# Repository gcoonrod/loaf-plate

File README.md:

# The LoafPlate

The LoafPlate is a DIY electronics and prototyping tool designed to make interacting with standard
(830 tie-point) breadboards easier. The base PCB is intended to be reused in other designs to allow for the
creation of "plates" (like Arduino shields or RPi hats), which can provide any number of features to support or interact with the LoafPlate and its breadboard.

## The LP Extension

Like the hats and shields that inspired it, the LoafPlate uses a "standard" or shared interface called an LP Extension. The LP Extension is designed to share power, ground, and six GPIO signals between any number of stacked plates. A 10 pin right angle IDC connector with 2.54mm pitch was chosen as it can be used with ribbon cables which are easy for hobbyists to buy or assemble.

Six GPIOs isn't much (not even a full byte!) but unlike an Arduino or Raspberry Pi the LoafPlate is focused
on supporting breadboard prototyping and its design is intended to leave as much open space around the edges of each plate as possible. This space will be used by other plates to provide easy access to sockets, pin headers, screw terminals, buttons, and more.

## The Standard Plates

Along with the LoafPlate, this repo contains designs for a number of other plates which are meant to provide an example of a complete (if simple) circuit prototyping environment or hardware IDE if you will.

### The PSUPlate

All electronics projects need power, as such the first accessory plate for the LoafPlate is the PSUPlate. As the name suggests, it is a power supply unit designed to connect to a common ATX power supply via the 24 pin ATX 2.0 connector. The PSUPlate provides access to 3.3V, 5V, and 12V power rails and uses readily available blade type fuses for circuit protection.

### The TestPlate

Interacting with digital circuits can be difficult and frustrating without tools like an oscilloscope or
logic analyzer. However, those tools can be quite expensive. The TestPlate is designed to act as a circuit
tester, allowing the user to drive two chains of shift registers which allows them to set 32 input values and read 32 output results.

This picture is from an early design of the TestPlate before the LP Extension was finalized.

## Extra Plates

The following are early designs and ideas for kinds of plates that can be created for the LoafPlate environment.

### The ClockPlate

Based on the work of Bed Eater and Rehsd, the ClockPlate is a clock signal generator for 5V logic circuits.
It provides three clocking modes: Manual pulse, Adjustable slow (555), and fixed fast (crystal oscillator). In addition to the standard LP Extension, it exposes two pair of outputs (clock and reset) and accepts a single input (halt).

## Project Goals

I am a software engineer by trade and training. Hardware and digital circuits have always seemed the realm of sorcerers and the dark arts to me. Watching YouTube videos from people like Ben Eater, Rehsd, and Francis Stokes (Low Byte Productions), has really opened my eyes to how accessible hardware and computer design has become. My goal for the LoafPlate project is above all, learning. I want to understand how the computers I write programs for _actually_ work and I want to design circuits, systems, and devices to help further that understanding.

This repo is my RFC, my Request for Comment. Please, point out my mistakes, correct my bad assumptions, suggest improvements, help me _learn_.

### Links & Resources

Tools:

- [KiCad](https://www.kicad.org/): All circuits and PCBs were designed with KiCad V6.

YouTube Creators:

- [Ben Eater](https://www.youtube.com/@BenEater)
- [Rehsd](https://www.youtube.com/@rehsd)
- [Low Byte Productions](https://www.youtube.com/@LowByteProductions)
- [Phil's Lab](https://www.youtube.com/@PhilsLab)
- [Fabian Schuiki](https://www.youtube.com/@fabianschuiki)
- [Adrien Kohlbecker](https://www.youtube.com/@akohlbecker)

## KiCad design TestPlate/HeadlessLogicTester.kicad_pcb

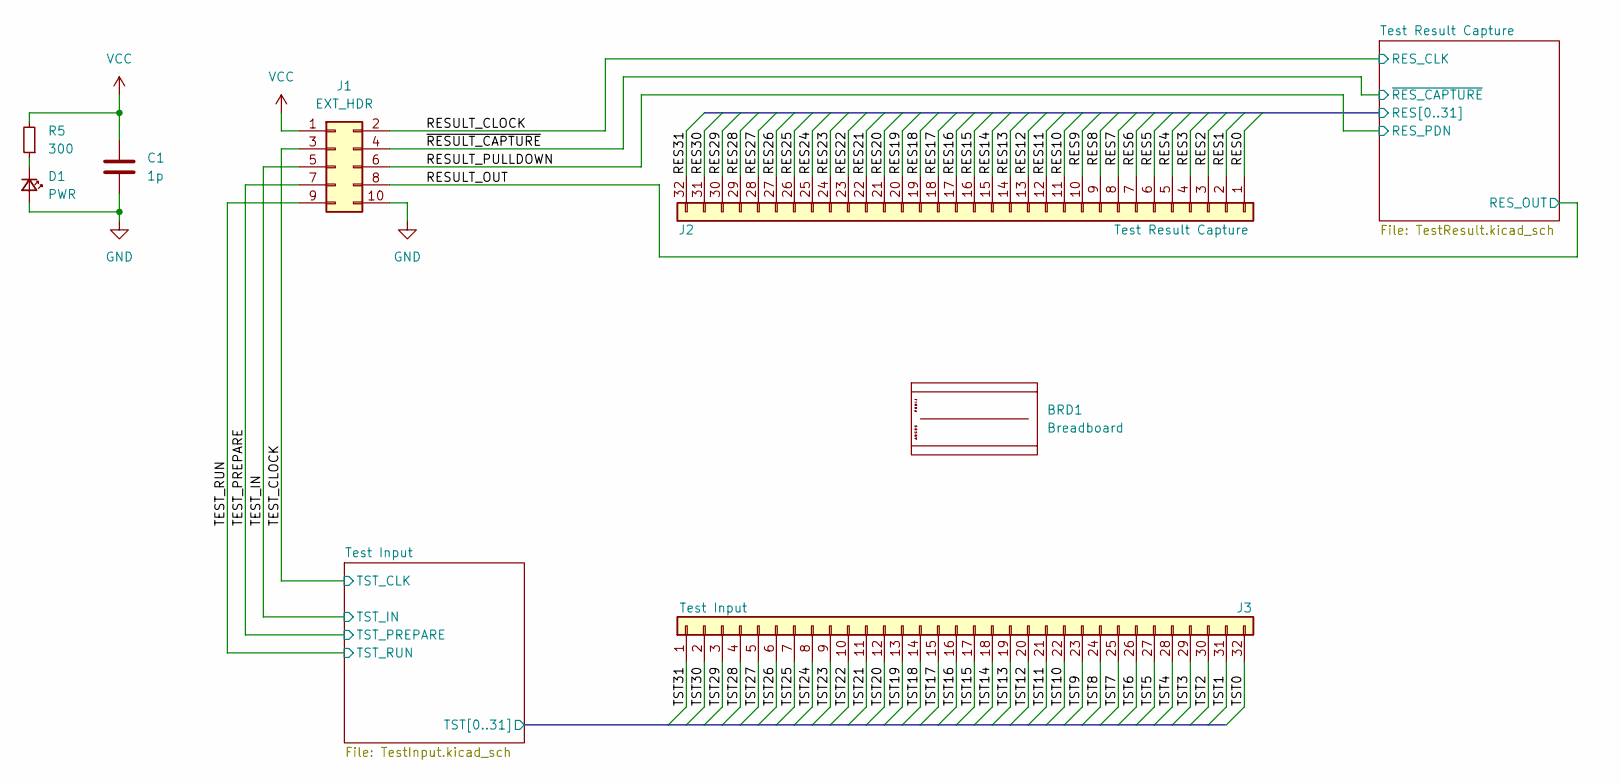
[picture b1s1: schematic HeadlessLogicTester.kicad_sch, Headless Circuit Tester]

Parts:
BRD1: Breadboard; Breadboard_Busx02_Terminalx01_Tiesx830_WithMounts
C1: 1p; C_1206_3216Metric_Pad1.33x1.80mm_HandSolder
D1: PWR; LED_1206_3216Metric_Pad1.42x1.75mm_HandSolder
J1: EXT_HDR; PinSocket_2x05_P2.54mm_Horizontal
J2: Test Result Capture; PinSocket_1x32_P2.54mm_Horizontal
J3: Test Input; PinSocket_1x32_P2.54mm_Horizontal
R5: 300; R_1206_3216Metric_Pad1.30x1.75mm_HandSolder

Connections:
/RESULT_CLOCK: J1.2; also elsewhere on the board
/RESULT_OUT: J1.8; also elsewhere on the board
/RESULT_PULLDOWN: J1.6; also elsewhere on the board
/TEST_CLOCK: J1.3; also elsewhere on the board
/TEST_IN: J1.5; also elsewhere on the board
/TEST_PREPARE: J1.7; also elsewhere on the board
/TEST_RUN: J1.9; also elsewhere on the board
/Test Input/TST0: J3.32; also elsewhere on the board
/Test Input/TST1: J3.31; also elsewhere on the board
/Test Input/TST2: J3.30; also elsewhere on the board
/Test Input/TST3: J3.29; also elsewhere on the board
/Test Input/TST4: J3.28; also elsewhere on the board
/Test Input/TST5: J3.27; also elsewhere on the board
/Test Input/TST6: J3.26; also elsewhere on the board
/Test Input/TST7: J3.25; also elsewhere on the board
/Test Input/TST8: J3.24; also elsewhere on the board
/Test Input/TST9: J3.23; also elsewhere on the board
/Test Input/TST10: J3.22; also elsewhere on the board
/Test Input/TST11: J3.21; also elsewhere on the board
/Test Input/TST12: J3.20; also elsewhere on the board
/Test Input/TST13: J3.19; also elsewhere on the board
/Test Input/TST14: J3.18; also elsewhere on the board
/Test Input/TST15: J3.17; also elsewhere on the board
/Test Input/TST16: J3.16; also elsewhere on the board
/Test Input/TST17: J3.15; also elsewhere on the board
/Test Input/TST18: J3.14; also elsewhere on the board
/Test Input/TST19: J3.13; also elsewhere on the board
/Test Input/TST20: J3.12; also elsewhere on the board
/Test Input/TST21: J3.11; also elsewhere on the board
/Test Input/TST22: J3.10; also elsewhere on the board
/Test Input/TST23: J3.9; also elsewhere on the board
/Test Input/TST24: J3.8; also elsewhere on the board
/Test Input/TST25: J3.7; also elsewhere on the board
/Test Input/TST26: J3.6; also elsewhere on the board
/Test Input/TST27: J3.5; also elsewhere on the board
/Test Input/TST28: J3.4; also elsewhere on the board
/Test Input/TST29: J3.3; also elsewhere on the board
/Test Input/TST30: J3.2; also elsewhere on the board
/Test Input/TST31: J3.1; also elsewhere on the board
/Test Result Capture/RES0: J2.1; also elsewhere on the board
/Test Result Capture/RES1: J2.2; also elsewhere on the board
/Test Result Capture/RES2: J2.3; also elsewhere on the board
/Test Result Capture/RES3: J2.4; also elsewhere on the board
/Test Result Capture/RES4: J2.5; also elsewhere on the board
/Test Result Capture/RES5: J2.6; also elsewhere on the board
/Test Result Capture/RES6: J2.7; also elsewhere on the board
/Test Result Capture/RES7: J2.8; also elsewhere on the board
/Test Result Capture/RES8: J2.9; also elsewhere on the board
/Test Result Capture/RES9: J2.10; also elsewhere on the board
/Test Result Capture/RES10: J2.11; also elsewhere on the board
/Test Result Capture/RES11: J2.12; also elsewhere on the board
/Test Result Capture/RES12: J2.13; also elsewhere on the board
/Test Result Capture/RES13: J2.14; also elsewhere on the board
/Test Result Capture/RES14: J2.15; also elsewhere on the board
/Test Result Capture/RES15: J2.16; also elsewhere on the board
/Test Result Capture/RES16: J2.17; also elsewhere on the board
/Test Result Capture/RES17: J2.18; also elsewhere on the board
/Test Result Capture/RES18: J2.19; also elsewhere on the board
/Test Result Capture/RES19: J2.20; also elsewhere on the board
/Test Result Capture/RES20: J2.21; also elsewhere on the board
/Test Result Capture/RES21: J2.22; also elsewhere on the board
/Test Result Capture/RES22: J2.23; also elsewhere on the board
/Test Result Capture/RES23: J2.24; also elsewhere on the board
/Test Result Capture/RES24: J2.25; also elsewhere on the board
/Test Result Capture/RES25: J2.26; also elsewhere on the board
/Test Result Capture/RES26: J2.27; also elsewhere on the board
/Test Result Capture/RES27: J2.28; also elsewhere on the board
/Test Result Capture/RES28: J2.29; also elsewhere on the board
/Test Result Capture/RES29: J2.30; also elsewhere on the board
/Test Result Capture/RES30: J2.31; also elsewhere on the board
/Test Result Capture/RES31: J2.32; also elsewhere on the board
/~RESULT_CAPTURE: J1.4; also elsewhere on the board
GND: C1.2, D1.2 (A), J1.10; also elsewhere on the board
unnamed: D1.1 (K), R5.1
VCC: C1.1, J1.1, R5.2; also elsewhere on the board

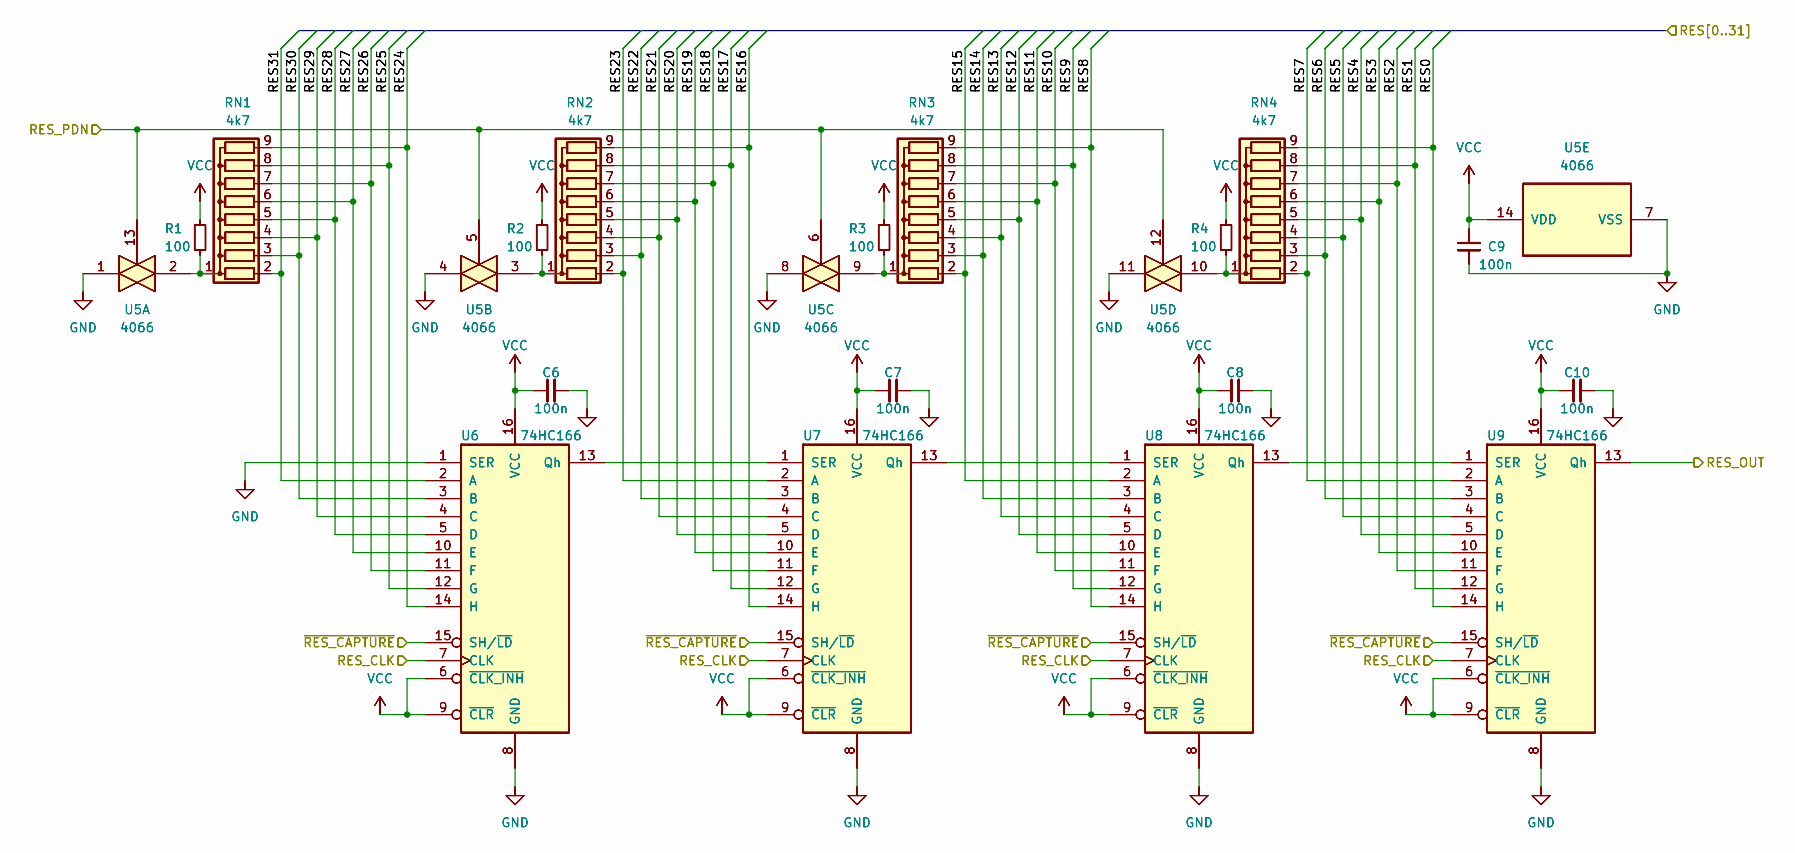
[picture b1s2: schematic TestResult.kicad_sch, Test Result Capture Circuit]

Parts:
C6, C7, C8, C9, C10: 100n; C_1206_3216Metric_Pad1.33x1.80mm_HandSolder
R1, R2, R3, R4: 100; C_1206_3216Metric_Pad1.33x1.80mm_HandSolder
RN1, RN2, RN3, RN4: 4k7; R_Array_SIP9
U5: 4066; DIP-14_W7.62mm_Socket
U6, U7, U8, U9: 74HC166; DIP-16_W7.62mm_Socket

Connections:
/RESULT_CLOCK: U6.7 (CLK), U7.7 (CLK), U8.7 (CLK), U9.7 (CLK); also elsewhere on the board
/RESULT_OUT: U9.13 (Qh); also elsewhere on the board
/RESULT_PULLDOWN: U5.5, U5.6, U5.12, U5.13; also elsewhere on the board
/Test Result Capture/RES0: RN4.9 (R8), U9.14 (H); also elsewhere on the board
/Test Result Capture/RES1: RN4.8 (R7), U9.12 (G); also elsewhere on the board
/Test Result Capture/RES2: RN4.7 (R6), U9.11 (F); also elsewhere on the board
/Test Result Capture/RES3: RN4.6 (R5), U9.10 (E); also elsewhere on the board
/Test Result Capture/RES4: RN4.5 (R4), U9.5 (D); also elsewhere on the board
/Test Result Capture/RES5: RN4.4 (R3), U9.4 (C); also elsewhere on the board
/Test Result Capture/RES6: RN4.3 (R2), U9.3 (B); also elsewhere on the board
/Test Result Capture/RES7: RN4.2 (R1), U9.2 (A); also elsewhere on the board
/Test Result Capture/RES8: RN3.9 (R8), U8.14 (H); also elsewhere on the board
/Test Result Capture/RES9: RN3.8 (R7), U8.12 (G); also elsewhere on the board
/Test Result Capture/RES10: RN3.7 (R6), U8.11 (F); also elsewhere on the board
/Test Result Capture/RES11: RN3.6 (R5), U8.10 (E); also elsewhere on the board
/Test Result Capture/RES12: RN3.5 (R4), U8.5 (D); also elsewhere on the board
/Test Result Capture/RES13: RN3.4 (R3), U8.4 (C); also elsewhere on the board
/Test Result Capture/RES14: RN3.3 (R2), U8.3 (B); also elsewhere on the board
/Test Result Capture/RES15: RN3.2 (R1), U8.2 (A); also elsewhere on the board
/Test Result Capture/RES16: RN2.9 (R8), U7.14 (H); also elsewhere on the board
/Test Result Capture/RES17: RN2.8 (R7), U7.12 (G); also elsewhere on the board
/Test Result Capture/RES18: RN2.7 (R6), U7.11 (F); also elsewhere on the board
/Test Result Capture/RES19: RN2.6 (R5), U7.10 (E); also elsewhere on the board
/Test Result Capture/RES20: RN2.5 (R4), U7.5 (D); also elsewhere on the board
/Test Result Capture/RES21: RN2.4 (R3), U7.4 (C); also elsewhere on the board
/Test Result Capture/RES22: RN2.3 (R2), U7.3 (B); also elsewhere on the board
/Test Result Capture/RES23: RN2.2 (R1), U7.2 (A); also elsewhere on the board
/Test Result Capture/RES24: RN1.9 (R8), U6.14 (H); also elsewhere on the board
/Test Result Capture/RES25: RN1.8 (R7), U6.12 (G); also elsewhere on the board
/Test Result Capture/RES26: RN1.7 (R6), U6.11 (F); also elsewhere on the board
/Test Result Capture/RES27: RN1.6 (R5), U6.10 (E); also elsewhere on the board
/Test Result Capture/RES28: RN1.5 (R4), U6.5 (D); also elsewhere on the board
/Test Result Capture/RES29: RN1.4 (R3), U6.4 (C); also elsewhere on the board
/Test Result Capture/RES30: RN1.3 (R2), U6.3 (B); also elsewhere on the board
/Test Result Capture/RES31: RN1.2 (R1), U6.2 (A); also elsewhere on the board
/~RESULT_CAPTURE: U6.15 (SH/~LD), U7.15 (SH/~LD), U8.15 (SH/~LD), U9.15 (SH/~LD); also elsewhere on the board
GND: C6.2, C7.2, C8.2, C9.2, C10.2, U5.1, U5.4, U5.7 (VSS), U5.8, U5.11, U6.1 (SER), U6.8 (GND), U7.8 (GND), U8.8 (GND), U9.8 (GND); also elsewhere on the board
unnamed: R1.2, RN1.1 (common), U5.2
unnamed: R2.2, RN2.1 (common), U5.3
unnamed: R3.2, RN3.1 (common), U5.9
unnamed: R4.2, RN4.1 (common), U5.10
unnamed: U6.13 (Qh), U7.1 (SER)
unnamed: U7.13 (Qh), U8.1 (SER)
unnamed: U8.13 (Qh), U9.1 (SER)
VCC: C6.1, C7.1, C8.1, C9.1, C10.1, R1.1, R2.1, R3.1, R4.1, U5.14 (VDD), U6.6 (~CLK_INH), U6.9 (~CLR), U6.16 (VCC), U7.6 (~CLK_INH), U7.9 (~CLR), U7.16 (VCC), U8.6 (~CLK_INH), U8.9 (~CLR), U8.16 (VCC), U9.6 (~CLK_INH), U9.9 (~CLR), U9.16 (VCC); also elsewhere on the board

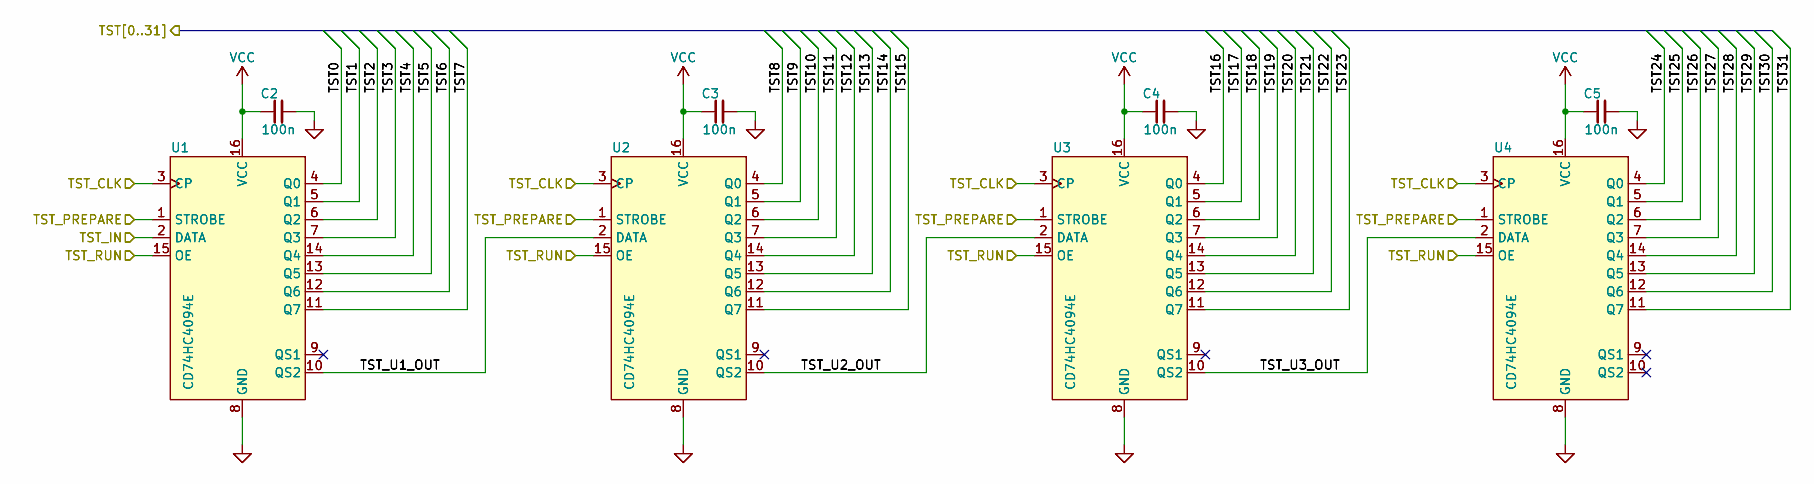
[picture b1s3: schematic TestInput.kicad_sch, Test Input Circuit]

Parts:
C2, C3, C4, C5: 100n; C_1206_3216Metric_Pad1.33x1.80mm_HandSolder
U1, U2, U3, U4: CD74HC4094E; DIP-16_W7.62mm_Socket

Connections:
/TEST_CLOCK: U1.3 (CP), U2.3 (CP), U3.3 (CP), U4.3 (CP); also elsewhere on the board
/TEST_IN: U1.2 (DATA); also elsewhere on the board
/TEST_PREPARE: U1.1 (STROBE), U2.1 (STROBE), U3.1 (STROBE), U4.1 (STROBE); also elsewhere on the board
/TEST_RUN: U1.15 (OE), U2.15 (OE), U3.15 (OE), U4.15 (OE); also elsewhere on the board
/Test Input/TST0: U1.4 (Q0); also elsewhere on the board
/Test Input/TST1: U1.5 (Q1); also elsewhere on the board
/Test Input/TST2: U1.6 (Q2); also elsewhere on the board
/Test Input/TST3: U1.7 (Q3); also elsewhere on the board
/Test Input/TST4: U1.14 (Q4); also elsewhere on the board
/Test Input/TST5: U1.13 (Q5); also elsewhere on the board
/Test Input/TST6: U1.12 (Q6); also elsewhere on the board
/Test Input/TST7: U1.11 (Q7); also elsewhere on the board
/Test Input/TST8: U2.4 (Q0); also elsewhere on the board
/Test Input/TST9: U2.5 (Q1); also elsewhere on the board
/Test Input/TST10: U2.6 (Q2); also elsewhere on the board
/Test Input/TST11: U2.7 (Q3); also elsewhere on the board
/Test Input/TST12: U2.14 (Q4); also elsewhere on the board
/Test Input/TST13: U2.13 (Q5); also elsewhere on the board
/Test Input/TST14: U2.12 (Q6); also elsewhere on the board
/Test Input/TST15: U2.11 (Q7); also elsewhere on the board
/Test Input/TST16: U3.4 (Q0); also elsewhere on the board
/Test Input/TST17: U3.5 (Q1); also elsewhere on the board
/Test Input/TST18: U3.6 (Q2); also elsewhere on the board
/Test Input/TST19: U3.7 (Q3); also elsewhere on the board
/Test Input/TST20: U3.14 (Q4); also elsewhere on the board
/Test Input/TST21: U3.13 (Q5); also elsewhere on the board
/Test Input/TST22: U3.12 (Q6); also elsewhere on the board
/Test Input/TST23: U3.11 (Q7); also elsewhere on the board
/Test Input/TST24: U4.4 (Q0); also elsewhere on the board
/Test Input/TST25: U4.5 (Q1); also elsewhere on the board
/Test Input/TST26: U4.6 (Q2); also elsewhere on the board
/Test Input/TST27: U4.7 (Q3); also elsewhere on the board
/Test Input/TST28: U4.14 (Q4); also elsewhere on the board
/Test Input/TST29: U4.13 (Q5); also elsewhere on the board
/Test Input/TST30: U4.12 (Q6); also elsewhere on the board
/Test Input/TST31: U4.11 (Q7); also elsewhere on the board
/Test Input/TST_U1_OUT: U1.10 (QS2), U2.2 (DATA)
/Test Input/TST_U2_OUT: U2.10 (QS2), U3.2 (DATA)
/Test Input/TST_U3_OUT: U3.10 (QS2), U4.2 (DATA)
GND: C2.2, C3.2, C4.2, C5.2, U1.8 (GND), U2.8 (GND), U3.8 (GND), U4.8 (GND); also elsewhere on the board
VCC: C2.1, C3.1, C4.1, C5.1, U1.16 (VCC), U2.16 (VCC), U3.16 (VCC), U4.16 (VCC); also elsewhere on the board

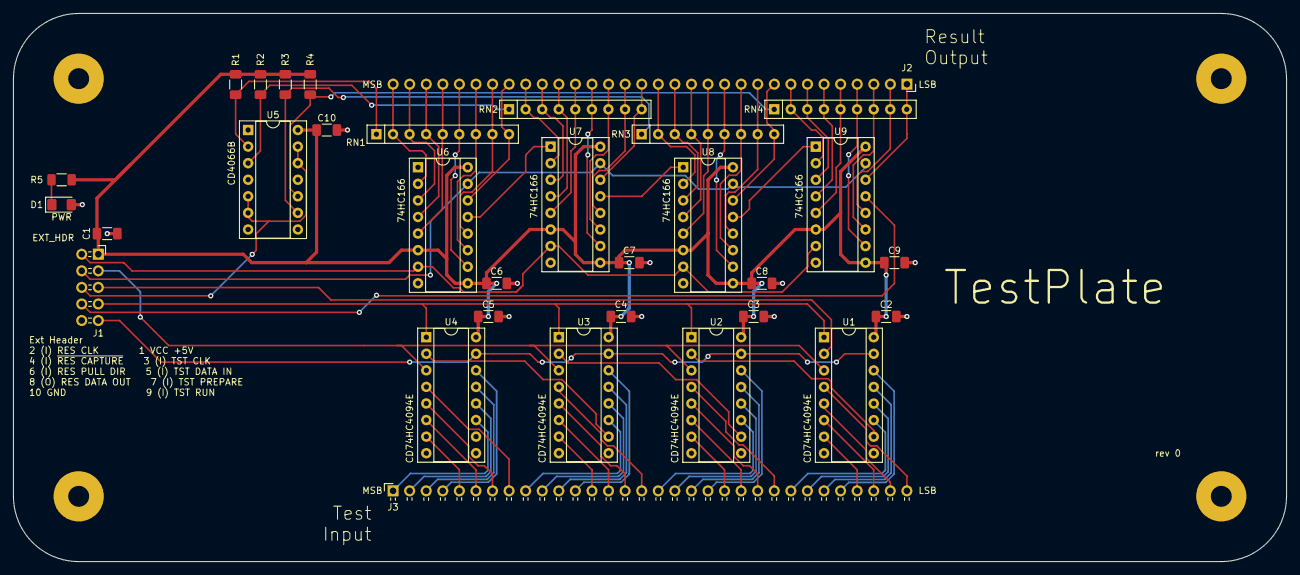
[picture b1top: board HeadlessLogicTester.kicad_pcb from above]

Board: 2 copper layers, 195.1 x 84.0 mm, 33 parts (0 on the bottom side), 85 nets.

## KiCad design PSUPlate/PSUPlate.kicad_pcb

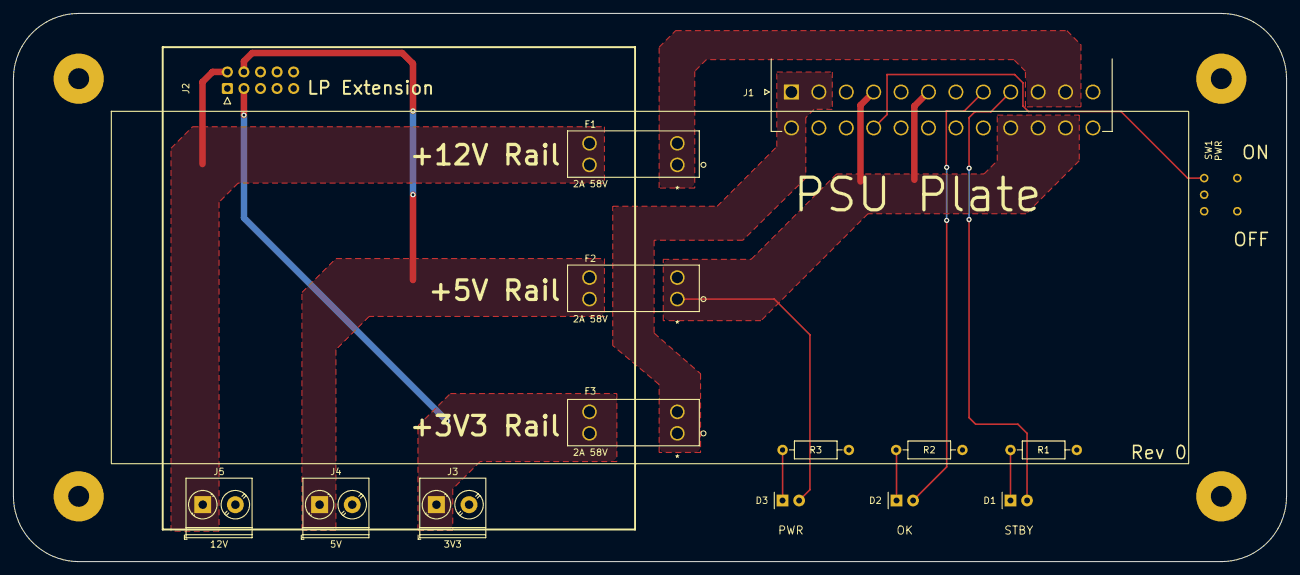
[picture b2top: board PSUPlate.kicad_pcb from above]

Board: 2 copper layers, 195.1 x 84.0 mm, 16 parts (0 on the bottom side), 13 nets.

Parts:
D1: STBY; LED_D5.0mm_FlatTop
D2: OK; LED_D5.0mm_FlatTop
D3: PWR; LED_D5.0mm_FlatTop
F1, F2, F3: 2A 58V; 3557-2
J1: ATX-24; MOLEX_469911024
J2: LP_EXT; IDC-Header_2x05_P2.54mm_Horizontal
J3: 3V3; TerminalBlock_Phoenix_PT-1,5-2-5.0-H_1x02_P5.00mm_Horizontal
J4: 5V; TerminalBlock_Phoenix_PT-1,5-2-5.0-H_1x02_P5.00mm_Horizontal
J5: 12V; TerminalBlock_Phoenix_PT-1,5-2-5.0-H_1x02_P5.00mm_Horizontal
PLT1: BasePlate; Breadboard_Busx02_Terminalx01_Tiesx830_WithMounts
R1, R2: 90; R_Axial_DIN0207_L6.3mm_D2.5mm_P10.16mm_Horizontal
R3: 220; R_Axial_DIN0207_L6.3mm_D2.5mm_P10.16mm_Horizontal
SW1: PWR; AS11CH

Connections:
+3.3V: F3.3, F3.4, J2.3 (3V3), J3.1
+5V: F2.3, F2.4, J2.4 (5V), J4.1
+12V: F1.3, F1.4, J2.2 (VCC), J5.1
/3V3: F3.1, F3.2, J1.1 (+3.3V), J1.2 (+3.3V), J1.13 (+3.3V)
/5V: D3.2 (A), F2.1, F2.2, J1.4 (+5V), J1.6 (+5V), J1.21 (+5V), J1.22 (+5V), J1.23 (+5V)
/5VSB: D1.2 (A), J1.9 (+5VSB)
/12V: F1.1, F1.2, J1.10 (+12V), J1.11 (+12V)
/PWR_OK: D2.2 (A), J1.8 (PWR_OK)
/~PS_ON: J1.16 (PS_ON#), SW1.3
GND: J1.3 (GND), J1.5 (GND), J1.7 (GND), J1.15 (GND), J1.17 (GND), J1.18 (GND), J1.19 (GND), J1.24 (GND), J2.1 (GND), J3.2, J4.2, J5.2, R1.2, R2.2, R3.2, SW1.1
unnamed: D1.1 (K), R1.1
unnamed: D2.1 (K), R2.1
unnamed: D3.1 (K), R3.1

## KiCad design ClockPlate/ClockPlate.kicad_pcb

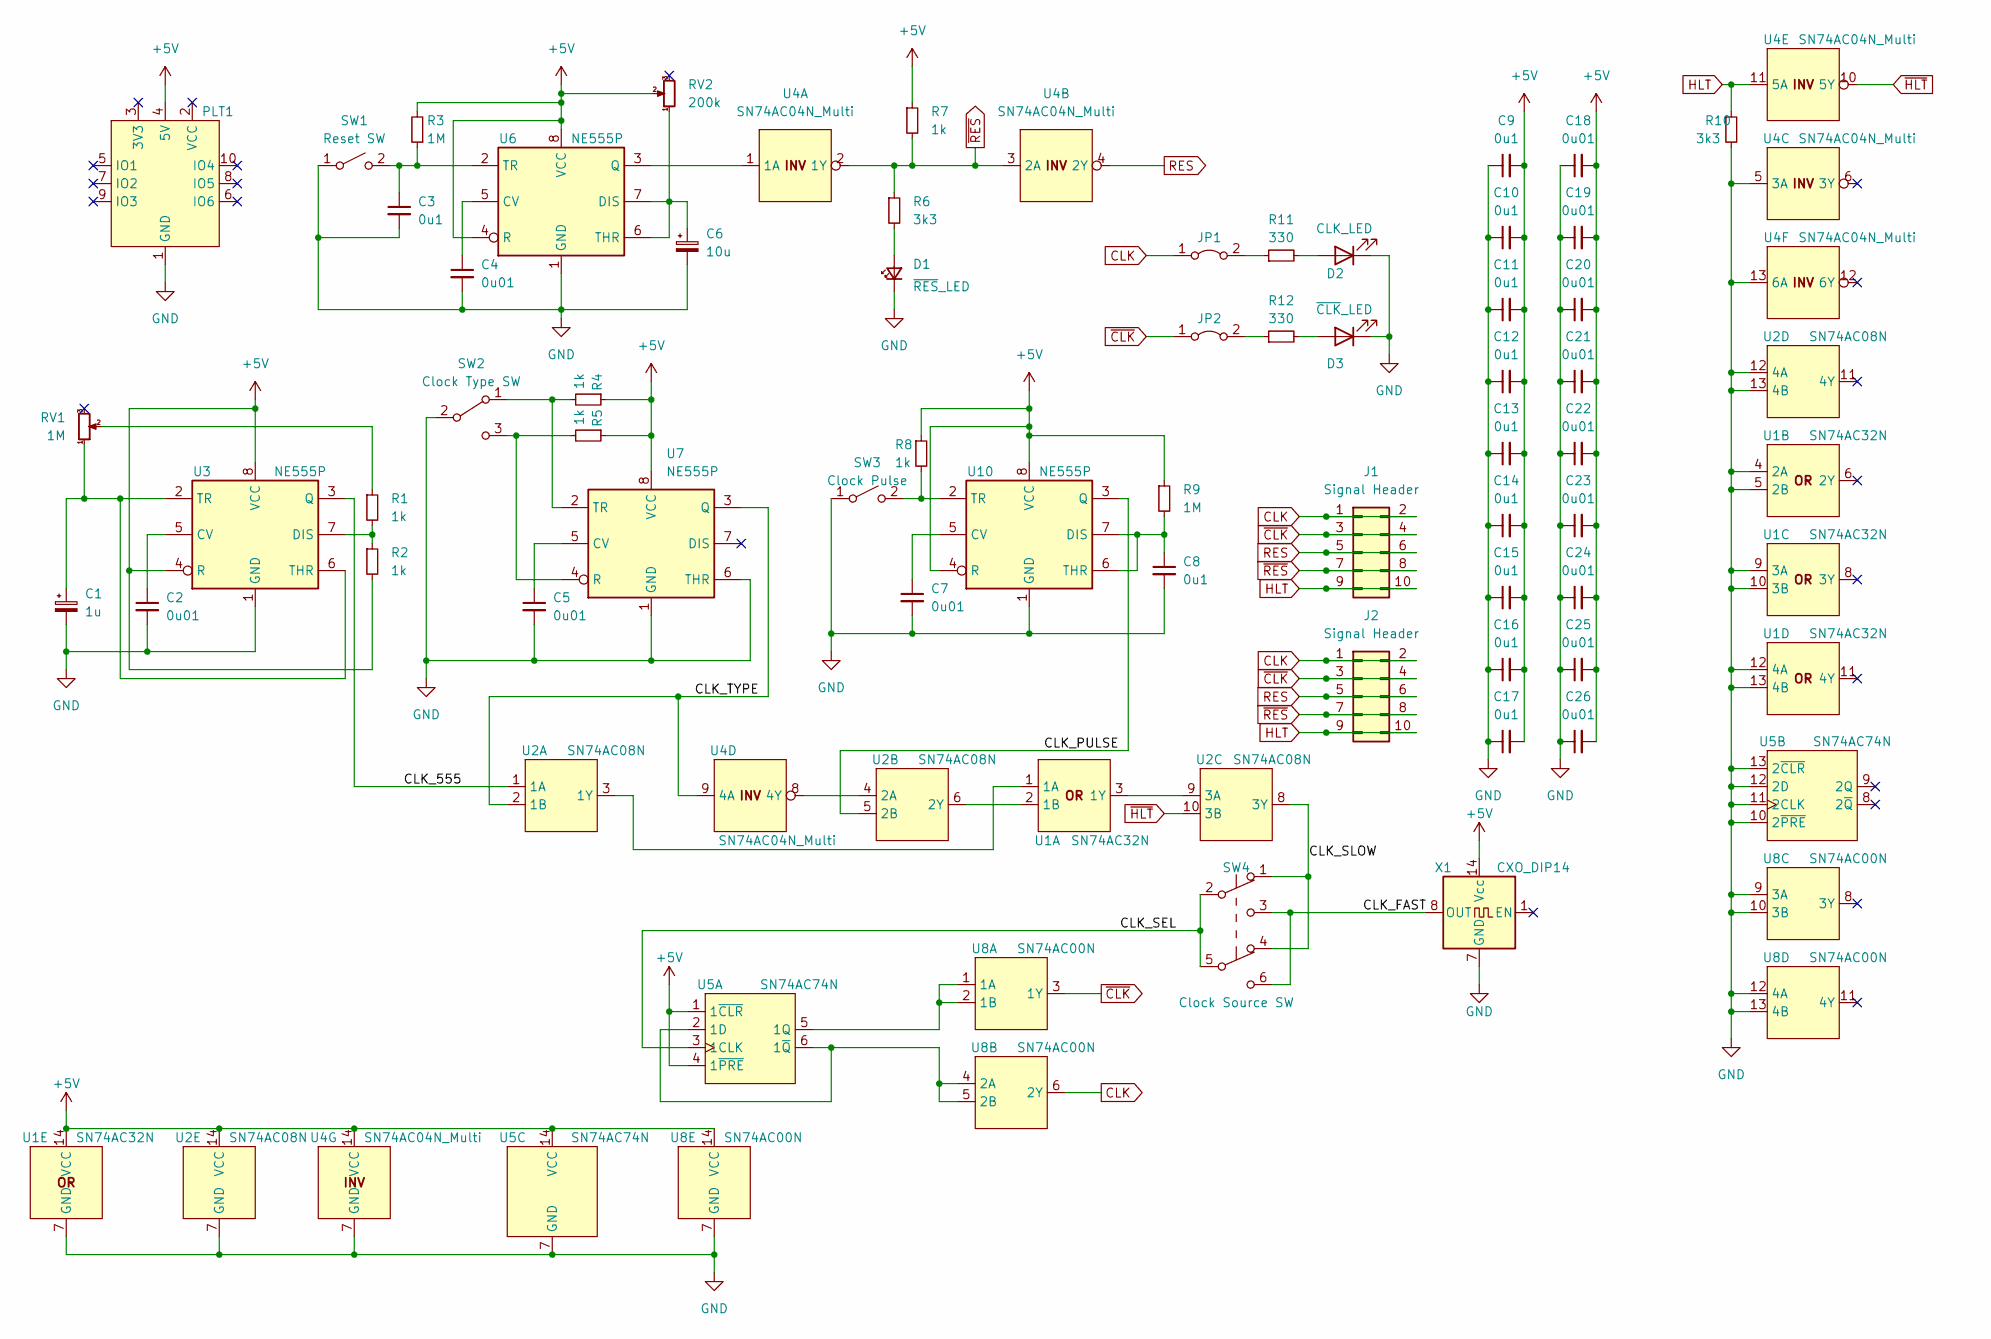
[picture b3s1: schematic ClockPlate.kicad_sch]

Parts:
C1: 1u; CP_Radial_D5.0mm_P2.00mm; Manufacturer Part Number 860020772005
C2, C4, C5, C7, C18, C19, C20, C21, C22, C23, C24, C25, C26: 0u01; C_Rect_L4.0mm_W2.5mm_P2.50mm; Manufacturer Part Number C315C103J3G5TA
C3, C8, C9, C10, C11, C12, C13, C14, C15, C16, C17: 0u1; C_Rect_L4.0mm_W2.5mm_P2.50mm; Manufacturer Part Number K104Z15Y5VE5TL2
C6: 10u; CP_Radial_D6.3mm_P2.50mm; Manufacturer Part Number 870055673001
D1: ~{RES}_LED; LED_D5.0mm; Manufacturer Part Number XSDG23MB
D2: CLK_LED; LED_D5.0mm; Manufacturer Part Number XSCBD23MB
D3: ~{CLK}_LED; LED_D5.0mm; Manufacturer Part Number XSDG23MB
J1: Signal Header; LP_EXT; Manufacturer Part Number 302-R101
J2: Signal Header; PinSocket_2x05_P2.54mm_Vertical; Manufacturer Part Number 302-R101
JP1: CLK_LED_JMP; PinHeader_1x02_P2.54mm_Vertical; Manufacturer Part Number 68000-102HLF
JP2: ~{CLK}_LED_JMP; PinHeader_1x02_P2.54mm_Vertical; Manufacturer Part Number 68000-102HLF
PLT1: BasePlate_with_PL_Extension; BasePlate with Extension
R1, R2, R4, R5, R7, R8: 1k; R_Axial_DIN0207_L6.3mm_D2.5mm_P10.16mm_Horizontal; Manufacturer Part Number YR1B1K0CC
R3, R9: 1M; R_Axial_DIN0207_L6.3mm_D2.5mm_P10.16mm_Horizontal; Manufacturer Part Number YR1B1M0CC
R6, R10: 3k3; R_Axial_DIN0207_L6.3mm_D2.5mm_P10.16mm_Horizontal; Manufacturer Part Number MFP-25BRD52-3K3
R11, R12: 330; R_Axial_DIN0207_L6.3mm_D2.5mm_P10.16mm_Horizontal; Manufacturer Part Number CFR16J330R
RV1: 1M; Potentiometer_Bourns_3386X_Horizontal; Manufacturer Part Number 3386X-1-105TLF
RV2: 200k; Potentiometer_Bourns_3266W_Vertical; Manufacturer Part Number 3266W-1-204LF
SW1: Reset SW; SW_PUSH_6mm; Manufacturer Part Number B3F-1002
SW2: Clock Type SW; SW_E-Switch_EG1271_DPDT; Manufacturer Part Number EG1271
SW3: Clock Pulse; SW_PUSH_6mm; Manufacturer Part Number B3F-1002
SW4: Clock Source SW; SW_E-Switch_EG1271_DPDT; Manufacturer Part Number EG1271
U1: SN74AC32N; DIP-14_W7.62mm_Socket_LongPads; Manufacturer Part Number SN74AC32N
U2: SN74AC08N; DIP-14_W7.62mm_Socket_LongPads; Manufacturer Part Number SN74AC08N
U3, U6, U7, U10: NE555P; DIP-8_W7.62mm_Socket_LongPads; Manufacturer Part Number NE555P
U4: SN74AC04N_Multi; DIP-14_W7.62mm_Socket_LongPads; Manufacturer Part Number SN74AC04N
U5: SN74AC74N; DIP-14_W7.62mm_Socket_LongPads; Manufacturer Part Number SN74AC74N
U8: SN74AC00N; DIP-14_W7.62mm_Socket_LongPads; Manufacturer Part Number SN74AC00N
X1: CXO_DIP14; Oscillator_DIP-14_LargePads

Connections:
+5V: C9.2, C10.2, C11.2, C12.2, C13.2, C14.2, C15.2, C16.2, C17.2, C18.2, C19.2, C20.2, C21.2, C22.2, C23.2, C24.2, C25.2, C26.2, PLT1.4 (5V), R2.2, R3.2, R4.1, R5.1, R7.1, R8.1, R9.1, RV2.2, U1.14 (VCC), U2.14 (VCC), U3.4 (R), U3.8 (VCC), U4.14 (VCC), U5.1 (1~CLR), U5.4 (1~PRE), U5.14 (VCC), U6.4 (R), U6.8 (VCC), U7.8 (VCC), U8.14 (VCC), U10.4 (R), U10.8 (VCC), X1.14 (Vcc)
/CLK_555: U2.1 (1A), U3.3 (Q)
/CLK_FAST: SW4.3 (C), SW4.6 (C), X1.8 (OUT)
/CLK_PULSE: U2.5 (2B), U10.3 (Q)
/CLK_SEL: SW4.2 (B), SW4.5 (B), U5.3 (1CLK)
/CLK_SLOW: SW4.1 (A), SW4.4 (A), U2.8 (3Y)
/CLK_TYPE: U2.2 (1B), U4.9 (4A), U7.3 (Q)
CLK: J1.1, J1.2, J2.1, J2.2, JP1.1 (A), U8.6 (2Y)
GND: C1.2, C2.2, C3.2, C4.2, C5.2, C6.2, C7.2, C8.2, C9.1, C10.1, C11.1, C12.1, C13.1, C14.1, C15.1, C16.1, C17.1, C18.1, C19.1, C20.1, C21.1, C22.1, C23.1, C24.1, C25.1, C26.1, D1.1 (K), D2.1 (K), D3.1 (K), PLT1.1 (GND), R10.2, SW1.1 (A), SW2.2 (B), SW3.1 (A), U1.4 (2A), U1.5 (2B), U1.7 (GND), U1.9 (3A), U1.10 (3B), U1.12 (4A), U1.13 (4B), U2.7 (GND), U2.12 (4A), U2.13 (4B), U3.1 (GND), U4.5 (3A), U4.7 (GND), U4.13 (6A), U5.7 (GND), U5.10 (2~PRE), U5.11 (2CLK), U5.12 (2D), U5.13 (2~CLR), U6.1 (GND), U7.1 (GND), U7.6 (THR), U8.7 (GND), U8.9 (3A), U8.10 (3B), U8.12 (4A), U8.13 (4B), U10.1 (GND), X1.7 (GND)
HLT: J1.9, J1.10, J2.9, J2.10, R10.1, U4.11 (5A)
unnamed: C1.1, RV1.1, U3.2 (TR), U3.6 (THR)
unnamed: C2.1, U3.5 (CV)
unnamed: C3.1, R3.1, SW1.2 (B), U6.2 (TR)
unnamed: C4.1, U6.5 (CV)
unnamed: C5.1, U7.5 (CV)
unnamed: C6.1, RV2.1, U6.6 (THR), U6.7 (DIS)
unnamed: C7.1, U10.5 (CV)
unnamed: C8.1, R9.2, U10.6 (THR), U10.7 (DIS)
unnamed: D1.2 (A), R6.2
unnamed: D2.2 (A), R11.2
unnamed: D3.2 (A), R12.2
unnamed: JP1.2 (B), R11.1
unnamed: JP2.2 (B), R12.1
unnamed: R1.1, RV1.2
unnamed: R1.2, R2.1, U3.7 (DIS)
unnamed: R4.2, SW2.1 (A), U7.2 (TR)
unnamed: R5.2, SW2.3 (C), U7.4 (R)
unnamed: R8.2, SW3.2 (B), U10.2 (TR)
unnamed: U1.1 (1A), U2.3 (1Y)
unnamed: U1.2 (1B), U2.6 (2Y)
unnamed: U1.3 (1Y), U2.9 (3A)
unnamed: U2.4 (2A), U4.8 (4Y)
unnamed: U5.2 (1D), U5.6 (1~Q), U8.4 (2A), U8.5 (2B)
unnamed: U5.5 (1Q), U8.1 (1A), U8.2 (1B)
unnamed: U4.1 (1A), U6.3 (Q)
RES: J1.5, J1.6, J2.5, J2.6, U4.4 (2Y)
~CLK: J1.3, J1.4, J2.3, J2.4, JP2.1 (A), U8.3 (1Y)
~HLT: U2.10 (3B), U4.10 (5Y)
~RES: J1.7, J1.8, J2.7, J2.8, R6.1, R7.2, U4.2 (1Y), U4.3 (2A)

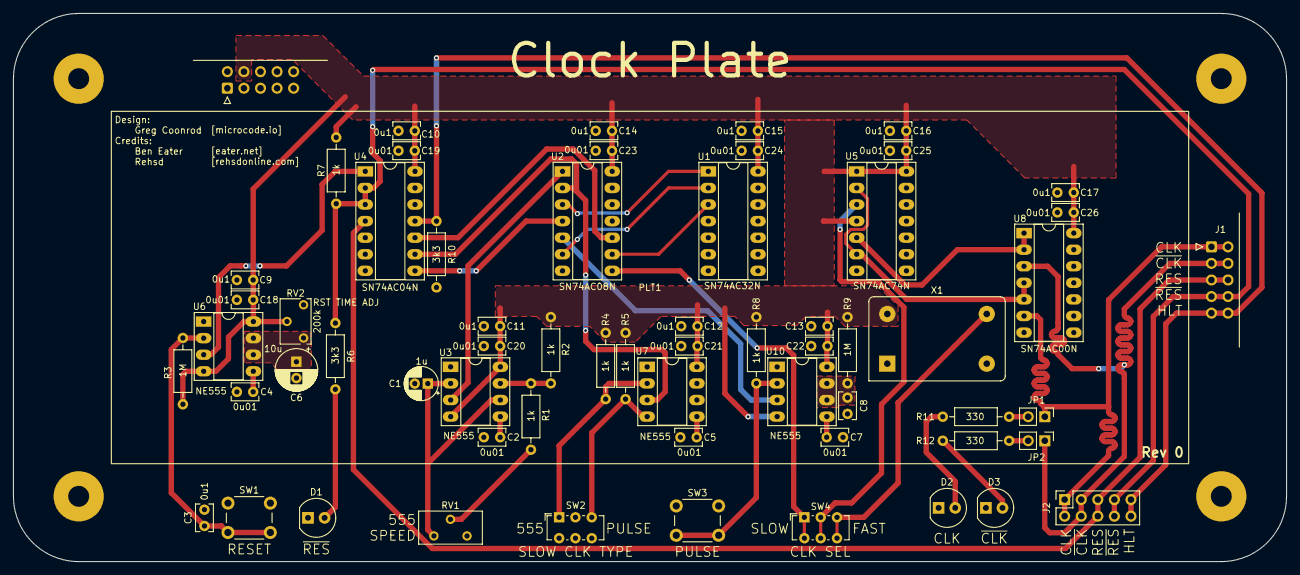
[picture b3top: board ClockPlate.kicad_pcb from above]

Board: 2 copper layers, 195.1 x 84.0 mm, 62 parts (0 on the bottom side), 39 nets.

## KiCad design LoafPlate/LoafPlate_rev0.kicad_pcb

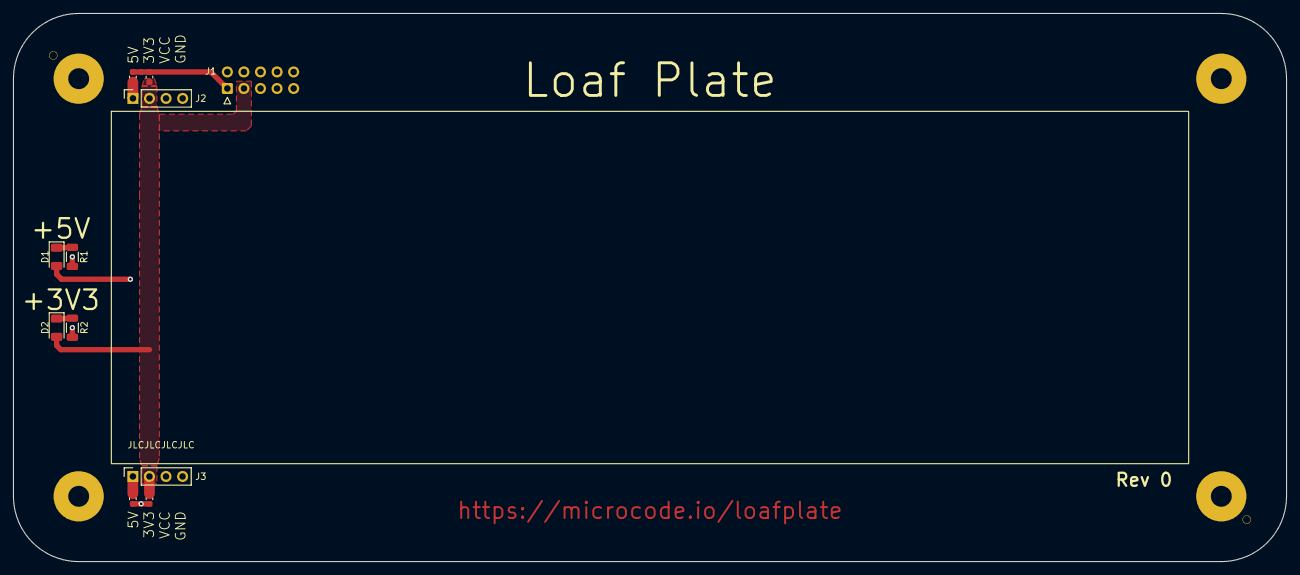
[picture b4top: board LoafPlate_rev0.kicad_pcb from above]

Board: 2 copper layers, 195.1 x 84.0 mm, 14 parts (0 on the bottom side), 6 nets.

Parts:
C1, C2, C3, C4: 100n; C_0603_1608Metric
D1: +5V_PWR; LED_1206_3216Metric
D2: +3V3_PWR; LED_1206_3216Metric
H1, H2: AssemblyToolingHole; JLCPCB_ToolingHole
J1: Ext Connector; IDC-Header_2x05_P2.54mm_Horizontal
J2, J3: Rail Power; PinSocket_1x04_P2.54mm_Vertical
PLT1: BasePlate; Breadboard_Busx02_Terminalx01_Tiesx830_WithMounts
R1: 120; R_1206_3216Metric
R2: 15; R_1206_3216Metric

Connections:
+3.3V: C3.1, C4.1, D2.2 (A), J1.3, J2.2, J3.2
+5V: C1.1, C2.1, D1.2 (A), J1.4, J2.1, J3.1
GND: C1.2, C2.2, C3.2, C4.2, J1.1, J2.4, J3.4, R1.2, R2.2
unnamed: D1.1 (K), R1.1
unnamed: D2.1 (K), R2.1
VCC: J1.2, J2.3, J3.3

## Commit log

2022-12-19 Add license
2022-12-20 Add rev 0 schematics and board designs
2022-12-20 Some directory cleanup and structuring.
2022-12-21 Minor power revisions
2022-12-23 Rev 0 of the PSUPlate
2022-12-27 Redo layout and routing
2022-12-27 Export schematic and 3D render.
2022-12-27 Added tooling holes for production.
2022-12-29 WIP ClockPlate
2022-12-30 First version of the ClockPlate schematic.
2022-12-31 Completed Rev0 of ClockPlate
2023-01-01 Readme update for rev0 sharing.

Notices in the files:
parts and their libraries:
Copyright 2021 Accelerated Designs. All rights reserved.
